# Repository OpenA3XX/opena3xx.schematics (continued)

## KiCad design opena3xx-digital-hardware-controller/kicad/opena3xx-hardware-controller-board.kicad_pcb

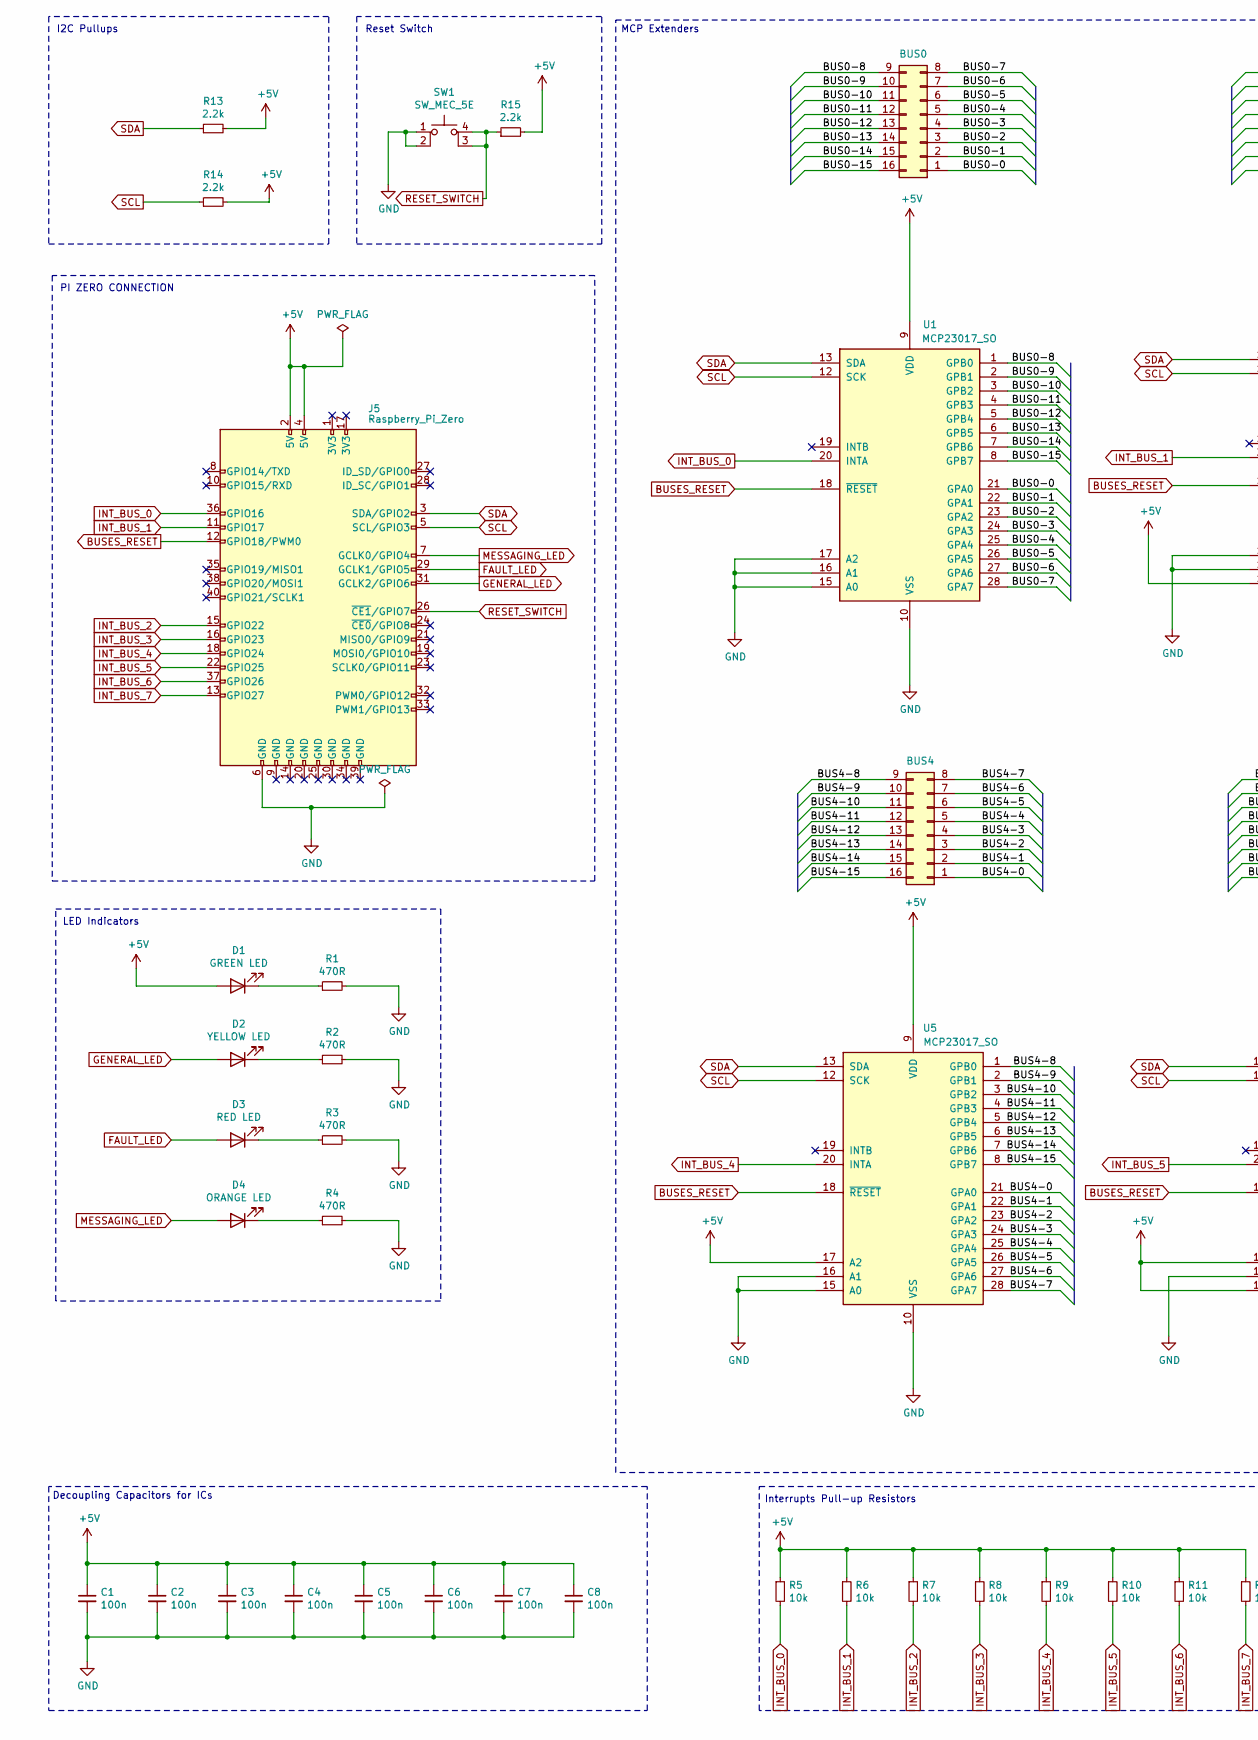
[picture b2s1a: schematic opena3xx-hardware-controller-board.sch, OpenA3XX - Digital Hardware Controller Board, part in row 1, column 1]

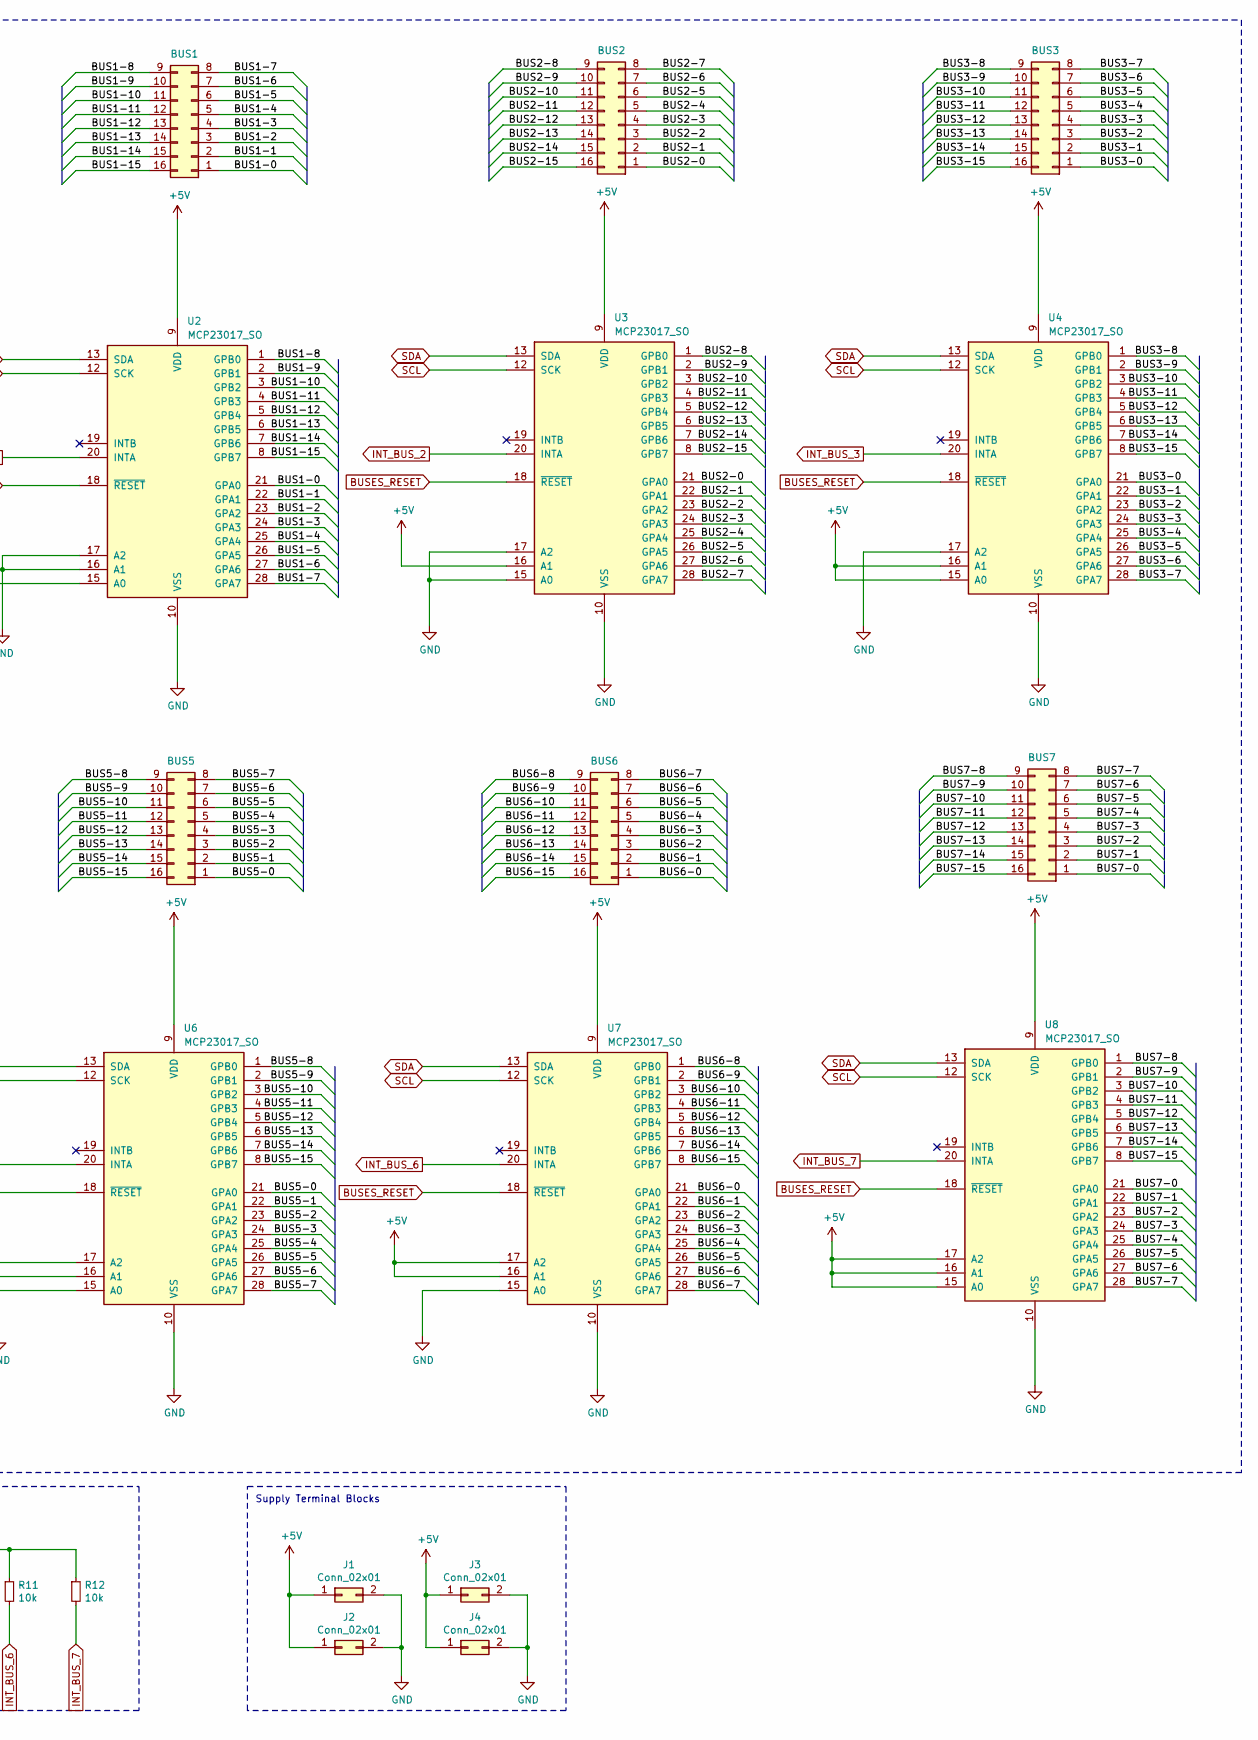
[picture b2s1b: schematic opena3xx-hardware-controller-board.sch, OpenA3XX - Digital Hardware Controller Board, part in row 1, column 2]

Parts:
BUS0, BUS1, BUS2, BUS3, BUS4, BUS5, BUS6, BUS7: Conn_02x08_Counter_Clockwise; PinHeader_2x08_P2.54mm_Vertical
C1, C2, C3, C4, C5, C6, C7, C8: 100n; C_1206_3216Metric_Pad1.33x1.80mm_HandSolder
D1: GREEN LED; D_1206_3216Metric_Pad1.42x1.75mm_HandSolder
D2: YELLOW LED; D_1206_3216Metric_Pad1.42x1.75mm_HandSolder
D3: RED LED; D_1206_3216Metric_Pad1.42x1.75mm_HandSolder
D4: ORANGE LED; D_1206_3216Metric_Pad1.42x1.75mm_HandSolder
J1, J2: Conn_02x01; PinHeader_1x02_P2.54mm_Vertical
J3, J4: Conn_02x01; TerminalBlock_bornier-2_P5.08mm
J5: Raspberry_Pi_Zero; PinHeader_2x20_P2.54mm_Vertical
R1, R2, R3, R4: 470R; R_1206_3216Metric_Pad1.30x1.75mm_HandSolder
R5, R6, R7, R8, R9, R10, R11, R12: 10k; R_1206_3216Metric_Pad1.30x1.75mm_HandSolder
R13, R14, R15: 2.2k; R_1206_3216Metric_Pad1.30x1.75mm_HandSolder
SW1: SW_MEC_5E; SW_Tactile_Straight_KSL0Axx1LFTR
U1, U2, U3, U4, U5, U6, U7, U8: MCP23017_SO; SOIC-28W_7.5x17.9mm_P1.27mm

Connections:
+5V: C1.1, C2.1, C3.1, C4.1, C5.1, C6.1, C7.1, C8.1, D1.2 (A), J1.1, J2.1, J3.1, J4.1, J5.2 (5V), J5.4 (5V), R5.1, R6.1, R7.1, R8.1, R9.1, R10.1, R11.1, R12.1, R13.2, R14.2, R15.2, U1.9 (VDD), U2.9 (VDD), U2.15 (A0), U3.9 (VDD), U3.16 (A1), U4.9 (VDD), U4.15 (A0), U4.16 (A1), U5.9 (VDD), U5.17 (A2), U6.9 (VDD), U6.15 (A0), U6.17 (A2), U7.9 (VDD), U7.16 (A1), U7.17 (A2), U8.9 (VDD), U8.15 (A0), U8.16 (A1), U8.17 (A2)
/BUS0-0: BUS0.1, U1.21 (GPA0)
/BUS0-1: BUS0.2, U1.22 (GPA1)
/BUS0-2: BUS0.3, U1.23 (GPA2)
/BUS0-3: BUS0.4, U1.24 (GPA3)
/BUS0-4: BUS0.5, U1.25 (GPA4)
/BUS0-5: BUS0.6, U1.26 (GPA5)
/BUS0-6: BUS0.7, U1.27 (GPA6)
/BUS0-7: BUS0.8, U1.28 (GPA7)
/BUS0-8: BUS0.9, U1.1 (GPB0)
/BUS0-9: BUS0.10, U1.2 (GPB1)
/BUS0-10: BUS0.11, U1.3 (GPB2)
/BUS0-11: BUS0.12, U1.4 (GPB3)
/BUS0-12: BUS0.13, U1.5 (GPB4)
/BUS0-13: BUS0.14, U1.6 (GPB5)
/BUS0-14: BUS0.15, U1.7 (GPB6)
/BUS0-15: BUS0.16, U1.8 (GPB7)
/BUS1-0: BUS1.1, U2.21 (GPA0)
/BUS1-1: BUS1.2, U2.22 (GPA1)
/BUS1-2: BUS1.3, U2.23 (GPA2)
/BUS1-3: BUS1.4, U2.24 (GPA3)
/BUS1-4: BUS1.5, U2.25 (GPA4)
/BUS1-5: BUS1.6, U2.26 (GPA5)
/BUS1-6: BUS1.7, U2.27 (GPA6)
/BUS1-7: BUS1.8, U2.28 (GPA7)
/BUS1-8: BUS1.9, U2.1 (GPB0)
/BUS1-9: BUS1.10, U2.2 (GPB1)
/BUS1-10: BUS1.11, U2.3 (GPB2)
/BUS1-11: BUS1.12, U2.4 (GPB3)
/BUS1-12: BUS1.13, U2.5 (GPB4)
/BUS1-13: BUS1.14, U2.6 (GPB5)
/BUS1-14: BUS1.15, U2.7 (GPB6)
/BUS1-15: BUS1.16, U2.8 (GPB7)
/BUS2-0: BUS2.1, U3.21 (GPA0)
/BUS2-1: BUS2.2, U3.22 (GPA1)
/BUS2-2: BUS2.3, U3.23 (GPA2)
/BUS2-3: BUS2.4, U3.24 (GPA3)
/BUS2-4: BUS2.5, U3.25 (GPA4)
/BUS2-5: BUS2.6, U3.26 (GPA5)
/BUS2-6: BUS2.7, U3.27 (GPA6)
/BUS2-7: BUS2.8, U3.28 (GPA7)
/BUS2-8: BUS2.9, U3.1 (GPB0)
/BUS2-9: BUS2.10, U3.2 (GPB1)
/BUS2-10: BUS2.11, U3.3 (GPB2)
/BUS2-11: BUS2.12, U3.4 (GPB3)
/BUS2-12: BUS2.13, U3.5 (GPB4)
/BUS2-13: BUS2.14, U3.6 (GPB5)
/BUS2-14: BUS2.15, U3.7 (GPB6)
/BUS2-15: BUS2.16, U3.8 (GPB7)
/BUS3-0: BUS3.1, U4.21 (GPA0)
/BUS3-1: BUS3.2, U4.22 (GPA1)
/BUS3-2: BUS3.3, U4.23 (GPA2)
/BUS3-3: BUS3.4, U4.24 (GPA3)
/BUS3-4: BUS3.5, U4.25 (GPA4)
/BUS3-5: BUS3.6, U4.26 (GPA5)
/BUS3-6: BUS3.7, U4.27 (GPA6)
/BUS3-7: BUS3.8, U4.28 (GPA7)
/BUS3-8: BUS3.9, U4.1 (GPB0)
/BUS3-9: BUS3.10, U4.2 (GPB1)
/BUS3-10: BUS3.11, U4.3 (GPB2)
/BUS3-11: BUS3.12, U4.4 (GPB3)
/BUS3-12: BUS3.13, U4.5 (GPB4)
/BUS3-13: BUS3.14, U4.6 (GPB5)
/BUS3-14: BUS3.15, U4.7 (GPB6)
/BUS3-15: BUS3.16, U4.8 (GPB7)
/BUS4-0: BUS4.1, U5.21 (GPA0)
/BUS4-1: BUS4.2, U5.22 (GPA1)
/BUS4-2: BUS4.3, U5.23 (GPA2)
/BUS4-3: BUS4.4, U5.24 (GPA3)
/BUS4-4: BUS4.5, U5.25 (GPA4)
/BUS4-5: BUS4.6, U5.26 (GPA5)
/BUS4-6: BUS4.7, U5.27 (GPA6)
/BUS4-7: BUS4.8, U5.28 (GPA7)
/BUS4-8: BUS4.9, U5.1 (GPB0)
/BUS4-9: BUS4.10, U5.2 (GPB1)
/BUS4-10: BUS4.11, U5.3 (GPB2)
/BUS4-11: BUS4.12, U5.4 (GPB3)
/BUS4-12: BUS4.13, U5.5 (GPB4)
/BUS4-13: BUS4.14, U5.6 (GPB5)
/BUS4-14: BUS4.15, U5.7 (GPB6)
/BUS4-15: BUS4.16, U5.8 (GPB7)
/BUS5-0: BUS5.1, U6.21 (GPA0)
/BUS5-1: BUS5.2, U6.22 (GPA1)
/BUS5-2: BUS5.3, U6.23 (GPA2)
/BUS5-3: BUS5.4, U6.24 (GPA3)
/BUS5-4: BUS5.5, U6.25 (GPA4)
/BUS5-5: BUS5.6, U6.26 (GPA5)
/BUS5-6: BUS5.7, U6.27 (GPA6)
/BUS5-7: BUS5.8, U6.28 (GPA7)
/BUS5-8: BUS5.9, U6.1 (GPB0)
/BUS5-9: BUS5.10, U6.2 (GPB1)
/BUS5-10: BUS5.11, U6.3 (GPB2)
/BUS5-11: BUS5.12, U6.4 (GPB3)
/BUS5-12: BUS5.13, U6.5 (GPB4)
/BUS5-13: BUS5.14, U6.6 (GPB5)
/BUS5-14: BUS5.15, U6.7 (GPB6)
/BUS5-15: BUS5.16, U6.8 (GPB7)
/BUS6-0: BUS6.1, U7.21 (GPA0)
/BUS6-1: BUS6.2, U7.22 (GPA1)
/BUS6-2: BUS6.3, U7.23 (GPA2)
/BUS6-3: BUS6.4, U7.24 (GPA3)
/BUS6-4: BUS6.5, U7.25 (GPA4)
/BUS6-5: BUS6.6, U7.26 (GPA5)
/BUS6-6: BUS6.7, U7.27 (GPA6)
/BUS6-7: BUS6.8, U7.28 (GPA7)
/BUS6-8: BUS6.9, U7.1 (GPB0)
/BUS6-9: BUS6.10, U7.2 (GPB1)
/BUS6-10: BUS6.11, U7.3 (GPB2)
/BUS6-11: BUS6.12, U7.4 (GPB3)
/BUS6-12: BUS6.13, U7.5 (GPB4)
/BUS6-13: BUS6.14, U7.6 (GPB5)
/BUS6-14: BUS6.15, U7.7 (GPB6)
/BUS6-15: BUS6.16, U7.8 (GPB7)
/BUS7-0: BUS7.1, U8.21 (GPA0)
/BUS7-1: BUS7.2, U8.22 (GPA1)
/BUS7-2: BUS7.3, U8.23 (GPA2)
/BUS7-3: BUS7.4, U8.24 (GPA3)
/BUS7-4: BUS7.5, U8.25 (GPA4)
/BUS7-5: BUS7.6, U8.26 (GPA5)
/BUS7-6: BUS7.7, U8.27 (GPA6)
/BUS7-7: BUS7.8, U8.28 (GPA7)
/BUS7-8: BUS7.9, U8.1 (GPB0)
/BUS7-9: BUS7.10, U8.2 (GPB1)
/BUS7-10: BUS7.11, U8.3 (GPB2)
/BUS7-11: BUS7.12, U8.4 (GPB3)
/BUS7-12: BUS7.13, U8.5 (GPB4)
/BUS7-13: BUS7.14, U8.6 (GPB5)
/BUS7-14: BUS7.15, U8.7 (GPB6)
/BUS7-15: BUS7.16, U8.8 (GPB7)
BUSES_RESET: J5.12 (GPIO18/PWM0), U1.18 (~RESET~), U2.18 (~RESET~), U3.18 (~RESET~), U4.18 (~RESET~), U5.18 (~RESET~), U6.18 (~RESET~), U7.18 (~RESET~), U8.18 (~RESET~)
FAULT_LED: D3.2 (A), J5.29 (GCLK1/GPIO5)
GENERAL_LED: D2.2 (A), J5.31 (GCLK2/GPIO6)
GND: C1.2, C2.2, C3.2, C4.2, C5.2, C6.2, C7.2, C8.2, J1.2, J2.2, J3.2, J4.2, J5.6 (GND), R1.2, R2.2, R3.2, R4.2, SW1.1, SW1.2, U1.10 (VSS), U1.15 (A0), U1.16 (A1), U1.17 (A2), U2.10 (VSS), U2.16 (A1), U2.17 (A2), U3.10 (VSS), U3.15 (A0), U3.17 (A2), U4.10 (VSS), U4.17 (A2), U5.10 (VSS), U5.15 (A0), U5.16 (A1), U6.10 (VSS), U6.16 (A1), U7.10 (VSS), U7.15 (A0), U8.10 (VSS)
INT_BUS_0: J5.36 (GPIO16), R5.2, U1.20 (INTA)
INT_BUS_1: J5.11 (GPIO17), R6.2, U2.20 (INTA)
INT_BUS_2: J5.15 (GPIO22), R7.2, U3.20 (INTA)
INT_BUS_3: J5.16 (GPIO23), R8.2, U4.20 (INTA)
INT_BUS_4: J5.18 (GPIO24), R9.2, U5.20 (INTA)
INT_BUS_5: J5.22 (GPIO25), R10.2, U6.20 (INTA)
INT_BUS_6: J5.37 (GPIO26), R11.2, U7.20 (INTA)
INT_BUS_7: J5.13 (GPIO27), R12.2, U8.20 (INTA)
MESSAGING_LED: D4.2 (A), J5.7 (GCLK0/GPIO4)
unnamed: D1.1 (K), R1.1
unnamed: D2.1 (K), R2.1
unnamed: D3.1 (K), R3.1
unnamed: D4.1 (K), R4.1
RESET_SWITCH: J5.26 (~CE1~/GPIO7), R15.1, SW1.3 (K), SW1.4 (A)
SCL: J5.5 (SCL/GPIO3), R14.1, U1.12 (SCK), U2.12 (SCK), U3.12 (SCK), U4.12 (SCK), U5.12 (SCK), U6.12 (SCK), U7.12 (SCK), U8.12 (SCK)
SDA: J5.3 (SDA/GPIO2), R13.1, U1.13 (SDA), U2.13 (SDA), U3.13 (SDA), U4.13 (SDA), U5.13 (SDA), U6.13 (SDA), U7.13 (SDA), U8.13 (SDA)

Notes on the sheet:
I2C Pullups
LED Indicators
PI ZERO CONNECTION
MCP Extenders
Decoupling Capacitors for ICs
Interrupts Pull-up Resistors
Supply Terminal Blocks
Reset Switch

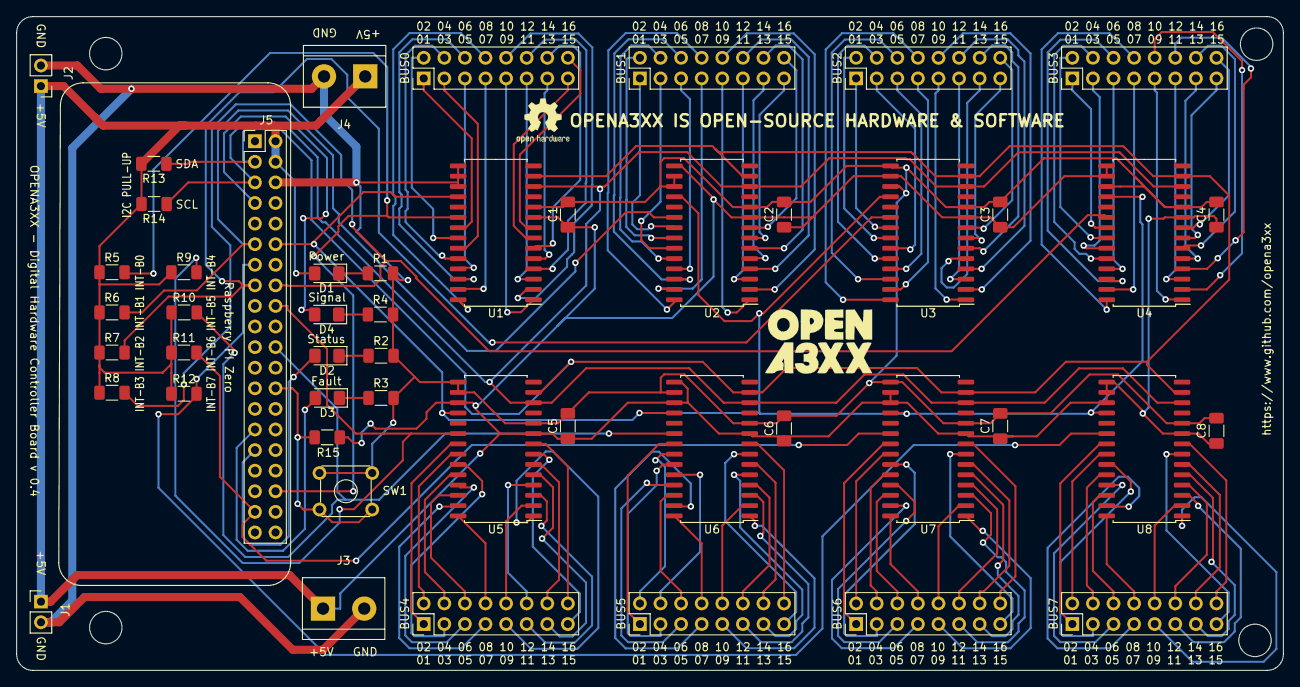
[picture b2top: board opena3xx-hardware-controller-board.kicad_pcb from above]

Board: 2 copper layers, 156.3 x 80.6 mm, 49 parts (0 on the bottom side), 149 nets.

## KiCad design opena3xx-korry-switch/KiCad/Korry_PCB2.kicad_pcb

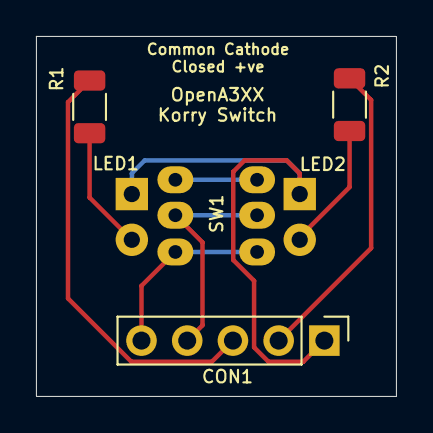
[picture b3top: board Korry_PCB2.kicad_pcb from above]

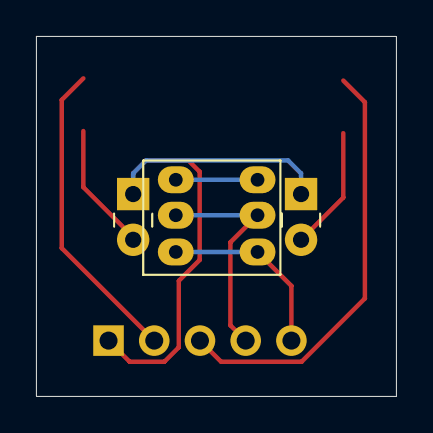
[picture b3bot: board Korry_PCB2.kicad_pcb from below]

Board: 2 copper layers, 20.0 x 20.0 mm, 6 parts (3 on the bottom side), 7 nets.

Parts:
CON1: Conn_01x05_MountingPin; PinHeader_1x05_P2.54mm_Vertical
LED1, LED2: LED; LED_Rectangular_W3.0mm_H2.0mm
R1, R2: 270; R_1206_3216Metric
SW1: S775-1; 6pin_Push_Button_Switch

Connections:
unnamed: CON1.1, LED1.1, LED2.1
unnamed: LED1.2, R1.1
unnamed: LED2.2, R2.1
unnamed: CON1.2, R2.2
unnamed: CON1.3, R1.2
unnamed: CON1.4, SW1.2
unnamed: CON1.5, SW1.1

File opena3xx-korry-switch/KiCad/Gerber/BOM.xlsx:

Comment | Designator | Footprint | LCSC Part #（optional）
270 | R1 | R_1206_3216Metric
270 | R2 | R_1206_3216Metric
1x5 2.54mm Vertical | CON1 | Conn_01x05_MountingPin

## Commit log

2021-01-28 Added MCDU Schematic WIP
2021-03-31 Updated Schematic
2021-04-10 Started OpenA3XX Hardware Controller
2021-04-10 Continuation of Digital Hardware Controller Schematic + PCB
2021-04-11 Hadware Controller Schematic v0.1 - Done
2021-04-11 Finalising PCB v 0.1
2021-04-11 Adding visuals
2021-04-11 Fixed DIL16 Connector (Was Flipped) Routed Manually BUS4
2021-04-11 Minor fixes
2021-04-12 Minor PCB IMprovements Fixed SDA/SCL Lines (Swapped in Schematic)
2021-04-13 Started Work on the MCDU Schematic Compelted Tactile with LED Packages
2021-04-16 Completed MCDU W/O IO Extenders (Designed to use OpenA3XX Digital Hardware Board)
2021-04-16 Added optional hardware board extender as part mcdu circuitry ( to have the option not to use an external extender board)
2021-04-17 Added 3d models for discrete components
2021-04-17 OpenA3XX PCB Laout completed. Track rounting pending!
2021-04-17 Improvements (MCDU Components Placement)
2021-04-18 Fixing issue with switches pinouts/leds - Rerouting
2021-04-18 MCDU Routed - Testing Pending
2021-04-18 Fixes Completed. PCB Routed: Manual verification tests PENDING - MCDU
2021-04-18 Updated thumbnails for readme
2021-04-19 Added OpenA3XX IO Terminal Block Board
2021-04-20 started v0.2 - implementing fixes after 0.1 prototype result
2021-04-21 Finalised v 0.2 and gerber generated
2021-04-21 Updated visualisation
2021-04-21 Minor updates
2021-05-01 Implementing v0.3 DHCB PCB (imporvements and minor fixes over v0.2)
2021-05-01 Added pullup resistors for Interrupts DHCB v0.3
2021-05-09 Adding digtal hardware controller v 0.4 in kicad
2021-05-09 DHCB Gerber V0.4
2021-05-10 Changed text from Messaging to Signal in Top Mask
2021-05-11 Created mcdu project in Kicad
2021-05-15 WIP Schematic & PCB for the MCDU Added custom Kicad Packages for the Tactile Switchs (LED EMBEDDED)
2021-05-15 Schematic Updates - MCDU
2021-05-15 Updated MCDU Schematic
2021-05-15 MCDU Updates
2021-05-16 Updates MCDU Schematic
2021-05-16 Completed MCDU Schematic v0.1
2021-05-22 Added readme file for DHC Board
2021-05-22 Fixed Silkscreen for the BUS connectors - from 1/16 to 0/15
2021-05-23 Updated MCDU PCB Layout for Tactile Switches completed.
2021-05-23 WIP PCB Layout process for MCDU - ICs and connectors
2021-05-24 Adding Contributing.md Minor imporvements to PCB
2021-05-24 Adding Code of Conduct
2021-05-24 Add files via upload
    Uploaded for readme files
2021-05-24 Continuation of MCDU PCB v0.1
2021-05-25 Updated PCB MCDU v0.1
2021-05-25 Finalised Layour for MCDU PCB v 0.1
2021-05-29 Fixing PCB dimensions for the MCDU
2021-05-29 Adding BOM as MD
2021-05-29 PCB MCDU changes
2021-05-30 Minor changes MCDU PCB
2021-05-30 Adding all buttons/led marking as Front Silk
2021-05-30 Finished all markings and moved also component reference to the right position.
2021-05-30 Minor Fix
2021-06-02 Fixed MCDU PCB with updated LSK RSK button Layout & Moved resistors to bottom of the PCB
2021-06-02 Removed vertical line of the screen (extra)
2021-06-06 Step file generation
    Step file generation
2021-06-10 Updated PCB - Latest updates for Back and Front Panel Design
2021-06-10 Added Libs + MCDU fixes + Added LCD Menu Tactile Switch
2021-06-12 Updates MCDU PCB
2021-06-13 Added tactile 3d model MCDU
2021-06-13 Fixed LED Markings + STP File Updated
2021-06-14 Adding MCDU STL (PCB)
    Adding MCDU STL (PCB)
2021-06-15 Adding @Kavster89 LCD Driver Board holes.
    Adding @Kavster89 LCD Driver Board holes.
2021-06-15 MCDU Improvements Markings + Added Tactile for LCD Power + LED funcational names
    MCDU Improvements Markings + Added Tactile for LCD Power + LED funcational names
2021-06-15 Slight modification to lcd driver board alignment
2021-06-17 PCB MCDU UPDATES
2021-06-17 Update LCD Driver Board Screws and Slot
2021-06-19 Tacking OpenA3XX MCDU
2021-06-19 Updating tracks and cleanup for MCDU
2021-06-20 Cleanup MCDU PCB
2021-06-20 WIP LED Backlight Widining
2021-06-21 opena3xx v0.1
2021-06-21 Restructuring of folders
2021-06-22 Korry Switch Added
    Added the KiCad directory for the Korry switch.
2021-07-01 Crating OpenA3XX Terminal Block PCB
2022-01-05 PCB Update
    1) 12V connecters moved up slightly to allow room for mounting nut.
    2) Connected the LED's for the 'LCD MENU' and 'LCD PWR'.
    3) Added 2 resistors for the 'LCD MENU' and 'LCD PWR' to allow direct connection to the display PCB.
2022-01-05 File restructure
    No change since last push.
2022-01-05 BOM & CPL
    BOM and CPL file created.
    They now also have the required part numbers for components.
